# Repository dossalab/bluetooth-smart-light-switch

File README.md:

# Bluetooth controlled cord light switch

**Before building, read this carefully (especially Safety guidelines)**

This project aims to create a remote-controlled, *smart* cord light switch. It has both physical control button and Bluetooth LE capabilities, allowing for a very natural user experience.

This repo contains both PCB design and firmware.

Hardware seems to work, but has barely been tested in the field. The high voltage part is rated at 220-230V / 50 Hz (European-ish standard). It should be trivial to recalculate the supply for the US standard.

The firmware was never fully developed, but `firmware` directory contains the current work-in-progress state to get you started.

**Make sure you know what you're doing. This project involves working with high voltages and requires advanced electronics experience. I'm not taking any responsibility for any damage arising from use of this device**

## Bringup

There are 4 solder pads underneath the board. You'll have to solder some wires to them in order to connect to the programming probe. Supply your own safe external power from your debugging probe or any other low-power source. **NEVER INTERFACE WITH THE DEVICE WHILE PLUGGED INTO MAINS POWER!**

The firmware is written in Rust and uses Embassy, the async framework with nrf-softdevice crate for BLE.

## Some safety guidelines

- Never touch any parts of the board while operational - you'd likely get a shock;
- Don't leave the device unattended for now - it's not stable enough to trust;
- Be in a good state of mind and pay attention to what you are doing - **it is easy to make mistakes and burn your stuff**

## Roadmap

- Proper case design (I just used one from the real switch, with drilled-out insides);
- HomeAssistant integration.

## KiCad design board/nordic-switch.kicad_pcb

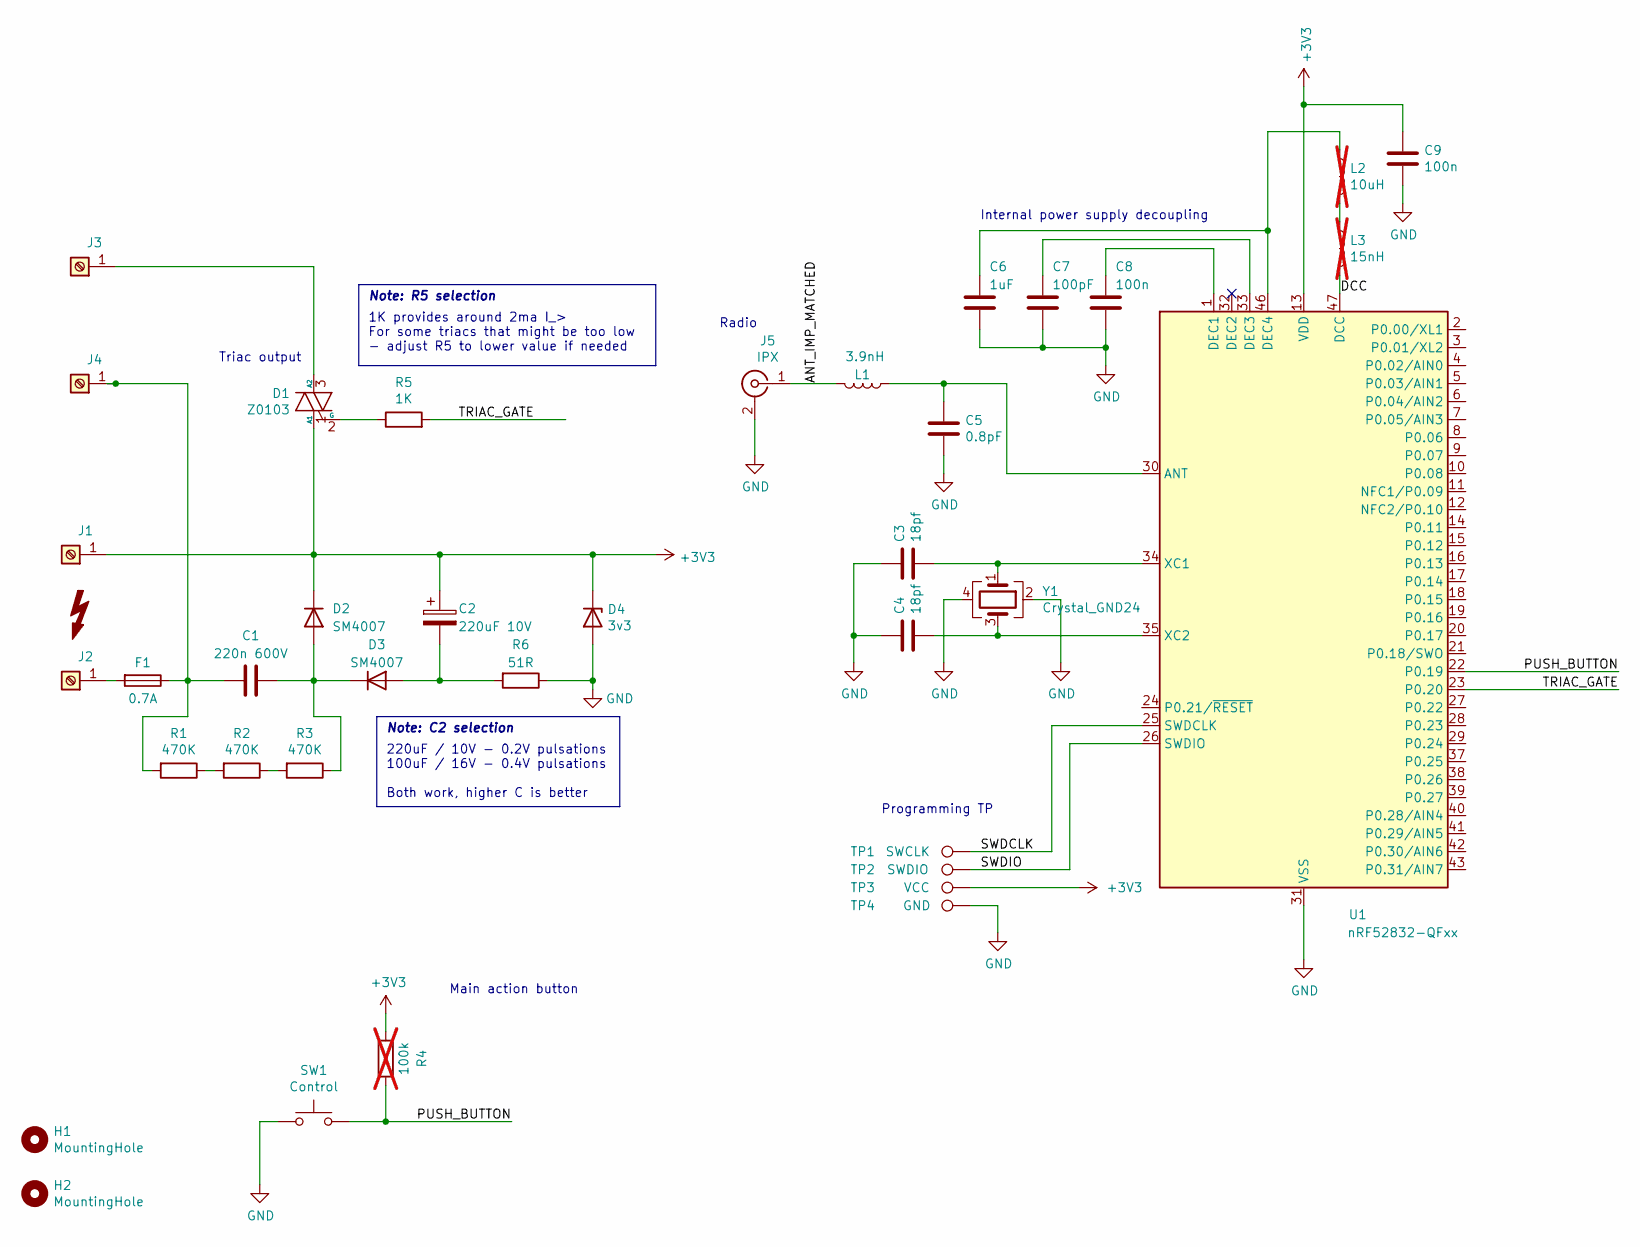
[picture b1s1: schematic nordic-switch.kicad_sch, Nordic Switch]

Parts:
C1: 220n 600V; CP_CBB_684J_400V_Flat
C2: 220uF 10V; CP_EIA-7343-30_AVX-N
C3, C4: 18pf; C_0603_1608Metric
C5: 0.8pF; C_0603_1608Metric
C6: 1uF; C_0603_1608Metric
C7: 100pF; C_0603_1608Metric
C8, C9: 100n; C_0603_1608Metric
D1: Z0103; TO-92_Inline_Wide
D2, D3: SM4007; D_MELF
D4: 3v3; D_MiniMELF
F1: 0.7A; Fuse_Littelfuse_395Series
H1, H2: MountingHole; MountingHole_3.2mm_M3
J1, J2, J3, J4: Screw_Terminal_01x01; SolderWire-1sqmm_1x01_D1.4mm_OD2.7mm
J5: IPX; U.FL_Hirose_U.FL-R-SMT-1_Vertical
L1: 3.9nH; L_0603_1608Metric
L2: 10uH; L_0805_2012Metric; not fitted
L3: 15nH; L_0603_1608Metric; not fitted
R1, R2, R3: 470K; R_1206_3216Metric
R4: 100k; R_0603_1608Metric; not fitted
R5: 1K; R_0603_1608Metric
R6: 51R; R_1206_3216Metric
SW1: Control; SW_SPST_PTS645
TP1: SWCLK; TestPoint_Pad_D1.0mm
TP2: SWDIO; TestPoint_Pad_D1.0mm
TP3: VCC; TestPoint_Pad_D1.0mm
TP4: GND; TestPoint_Pad_D1.0mm
U1: nRF52832-QFxx; QFN-48-1EP_6x6mm_P0.4mm_EP4.6x4.6mm
Y1: Crystal_GND24; Crystal_SMD_2520-4Pin_2.5x2.0mm

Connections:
+3V3: C2.1, C9.1, D1.1 (A1), D2.1 (K), D4.1 (K), J1.1, R4.2, TP3.1, U1.13 (VDD), U1.36 (VDD), U1.48 (VDD)
/ANT_IMP_MATCHED: J5.1 (In), L1.2
/DCC: L3.2, U1.47 (DCC)
/PUSH_BUTTON: R4.1, SW1.2, U1.22 (P0.19)
/SWDCLK: TP1.1, U1.25 (SWDCLK)
/SWDIO: TP2.1, U1.26 (SWDIO)
/TRIAC_GATE: R5.2, U1.23 (P0.20)
GND: C3.1, C4.1, C5.2, C6.2, C7.2, C8.2, C9.2, D4.2 (A), J5.2 (Ext), R6.1, SW1.1, TP4.1, U1.31 (VSS), U1.45 (VSS), U1.49 (VSS), Y1.2, Y1.4
unnamed: D1.3 (A2), J3.1
unnamed: D1.2 (G), R5.1
unnamed: C1.2, D2.2 (A), D3.1 (K), R3.1
unnamed: C2.2, D3.2 (A), R6.2
unnamed: F1.2, J2.1
unnamed: C1.1, F1.1, J4.1, R1.2
unnamed: L2.2, L3.1
unnamed: R1.1, R2.2
unnamed: R2.1, R3.2
unnamed: C5.1, L1.1, U1.30 (ANT)
unnamed: C8.1, U1.1 (DEC1)
unnamed: C7.1, U1.33 (DEC3)
unnamed: C6.1, L2.1, U1.46 (DEC4)
unnamed: C3.2, U1.34 (XC1), Y1.1
unnamed: C4.2, U1.35 (XC2), Y1.3

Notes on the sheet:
Triac output
Programming TP
Internal power supply decoupling
1K provides around 2ma I_{gt} For some triacs that might be too low - adjust R5 to lower value if needed
Main action button
Note: R5 selection
Note: C2 selection
Radio
220uF / 10V - 0.2V pulsations 100uF / 16V - 0.4V pulsations Both work, higher C is better

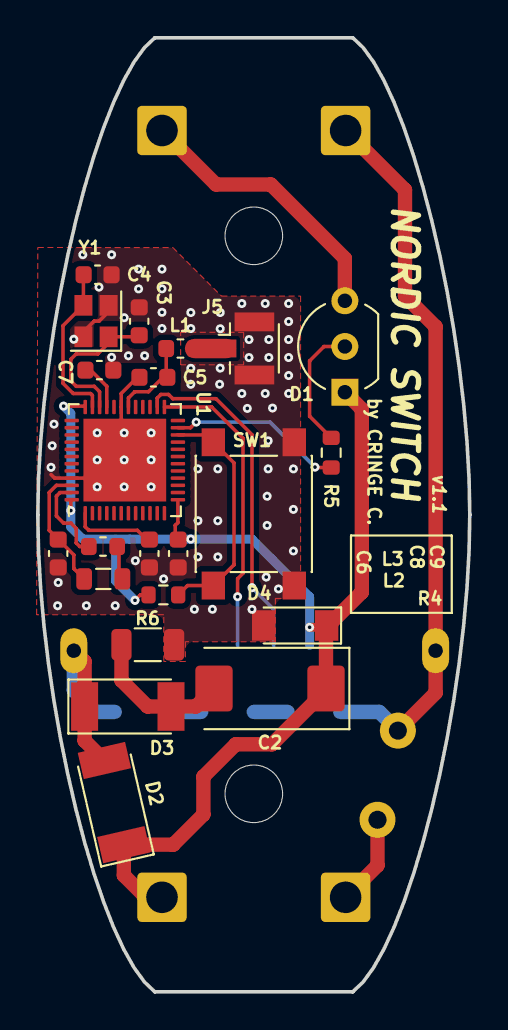
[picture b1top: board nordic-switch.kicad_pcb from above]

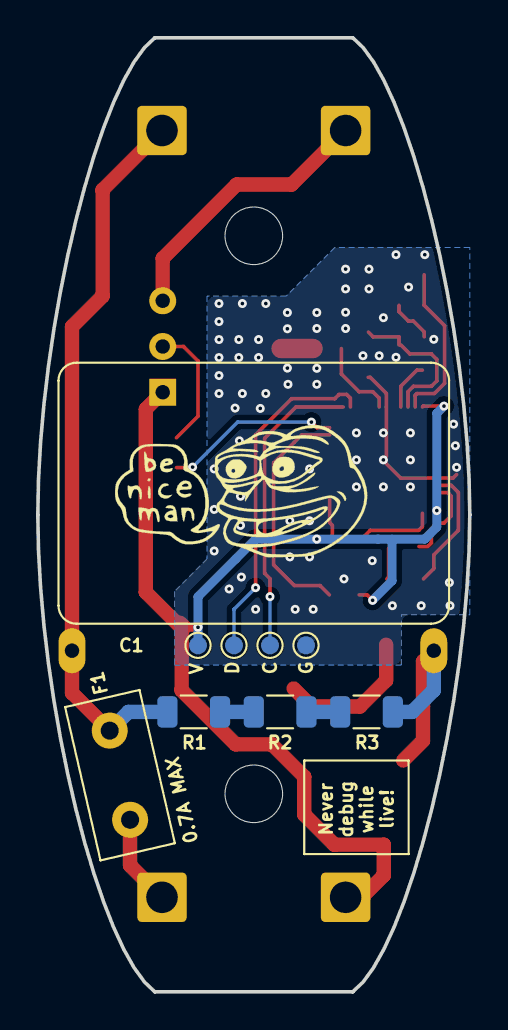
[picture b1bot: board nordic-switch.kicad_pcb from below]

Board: 2 copper layers, 24.0 x 53.0 mm, 37 parts (9 on the bottom side), 23 nets.

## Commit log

2020-03-24 Init commit
2024-10-03 update .gitignore for Kicad 6
2024-10-03 PCB version 1.1
    - Switched to Kicad 8
    - Better spacing for the high-voltage part
    - Re-route SWD from crystal area
2024-10-03 drop gerbers, docs, archives...
2024-10-03 add sample firmware
